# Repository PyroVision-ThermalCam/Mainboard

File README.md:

# PyroVision - Mainboard

## Table of Contents

- [PyroVision - Mainboard](#pyrovision---mainboard)
  - [Table of Contents](#table-of-contents)
  - [About](#about)
  - [License](#license)
  - [Maintainer](#maintainer)

## About

Mainboard for the PyroVision Open-Source Thermal Camera.

## License

This project is licensed under the GNU General Public License v3.0. See the [LICENSE](LICENSE) file for details.

## Maintainer

- [Daniel Kampert](mailto:daniel.kampert@kampis-elektroecke.de)

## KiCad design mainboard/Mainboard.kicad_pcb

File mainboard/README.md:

<h1 align="center">PyroVision Mainboard</h1>

<p align="center" width="100%">
  
</p>

***

<p align="center">
  
&nbsp; &nbsp; &nbsp; &nbsp;
  
</p>

***

## SPECIFICATIONS

| Parameter | Value |
| --- | --- |
| Dimensions | 32.0 × 24.0 mm |

***

## DIRECTORY STRUCTURE

    .
    ├─ Computations       # Misc calculations
    ├─ HTML               # HTML files for generated webpage
    ├─ Images             # Pictures and renders
    │
    ├─ kibot_resources    # External resources for KiBot
    │  ├─ colors          # Color theme for KiCad
    │  ├─ fonts           # Fonts used in the project
    │  ├─ scripts         # External scripts used with KiBot
    │  └─ templates       # Templates for KiBot generated reports
    │
    ├─ kibot_yaml         # KiBot YAML config files
    ├─ KiRI               # KiRI (PCB diff viewer) files
    │
    ├─ lib                # KiCad footprint and symbol libraries
    │  ├─ 3d_models       # Component 3D models
    │  ├─ lib_fp          # Footprint libraries
    │  └─ lib_sym         # Symbol libraries
    │
    ├─ logos              # Logos
    │
    ├─ Manufacturing      # Assembly and fabrication documents
    │  ├─ Assembly        # Assembly documents (BoM, pos, notes)
    │  │
    │  └─ Fabrication     # Fabrication documents (ZIP, notes)
    │     ├─ Drill Tables # CSV drill tables
    │     └─ Gerbers      # Gerbers
    │
    ├─ Report             # Reports for ERC/DRC
    ├─ Schematic          # PDF of schematic
    ├─ templates          # Title block templates
    ├─ Testing
    │  └─ Testpoints      # Testpoints tables
    │
    └─ Variants           # Outputs for assembly variants

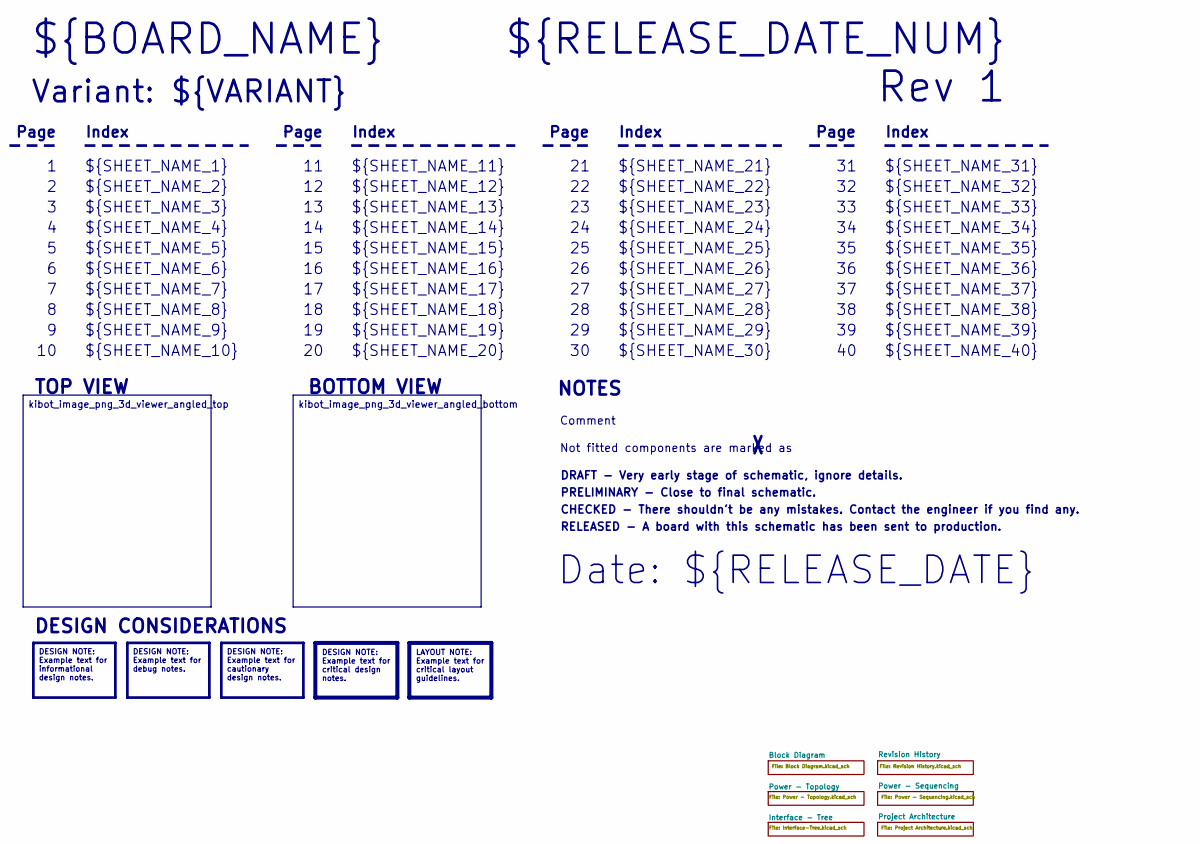
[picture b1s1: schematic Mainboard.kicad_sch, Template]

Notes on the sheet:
Variant: ${VARIANT}
RELEASED - A board with this schematic has been sent to production.
${SHEET_NAME_24}
Index
Page
PRELIMINARY - Close to final schematic.
${SHEET_NAME_22}
DRAFT - Very early stage of schematic, ignore details.
${SHEET_NAME_12}
${SHEET_NAME_8}
${SHEET_NAME_2}
${SHEET_NAME_5}
${SHEET_NAME_20}
${SHEET_NAME_23}
${RELEASE_DATE_NUM}
${SHEET_NAME_35}
Not fitted components are marked as
${SHEET_NAME_11}
${SHEET_NAME_6}
${SHEET_NAME_37}
${SHEET_NAME_26}
${SHEET_NAME_36}
Rev ${REVISION}
${SHEET_NAME_15}
CHECKED - There shouldn't be any mistakes. Contact the engineer if you find any.
BOTTOM VIEW
${SHEET_NAME_14}
${SHEET_NAME_21}
${SHEET_NAME_17}
${SHEET_NAME_18}
Date: ${RELEASE_DATE}
${SHEET_NAME_7}
${SHEET_NAME_31}
${BOARD_NAME}
NOTES
${SHEET_NAME_40}
${SHEET_NAME_39}
${SHEET_NAME_32}
${SHEET_NAME_1}
${SHEET_NAME_9}

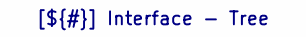
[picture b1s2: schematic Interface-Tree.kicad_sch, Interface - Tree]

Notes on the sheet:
[${#}] ${TITLE}

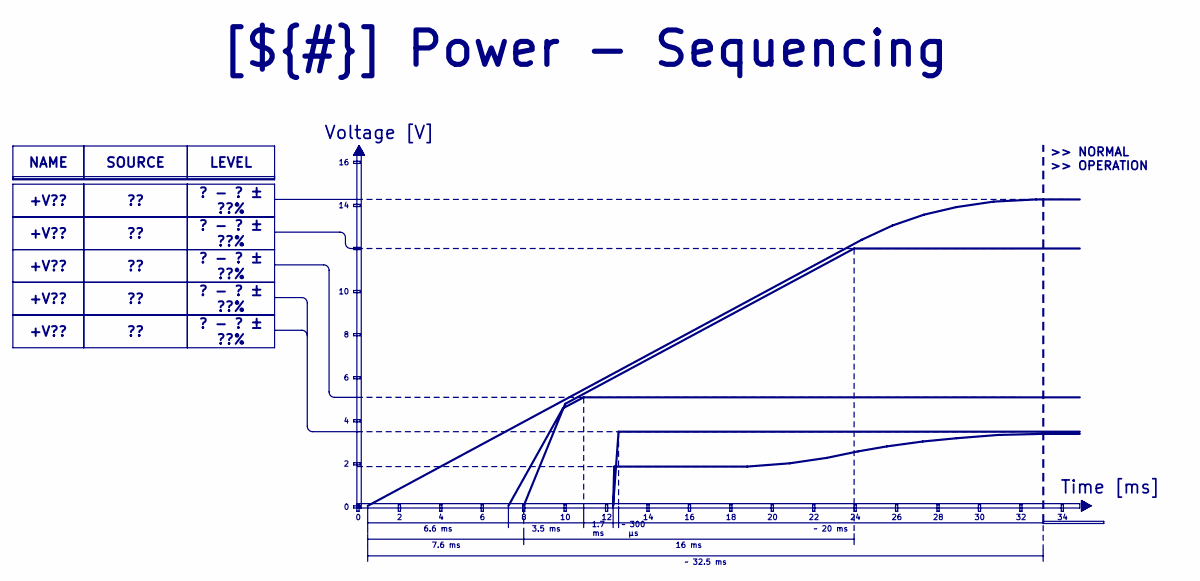
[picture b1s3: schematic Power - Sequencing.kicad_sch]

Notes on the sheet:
Voltage [V]
>> NORMAL >> OPERATION
Time [ms]
3.5 ms
7.6 ms
? - ? ± ??%
~ 300 μs
1.7 ms
16 ms
+V??
LEVEL
NAME
~ 20 ms
SOURCE
[${#}] ${TITLE}
6.6 ms
~ 32.5 ms

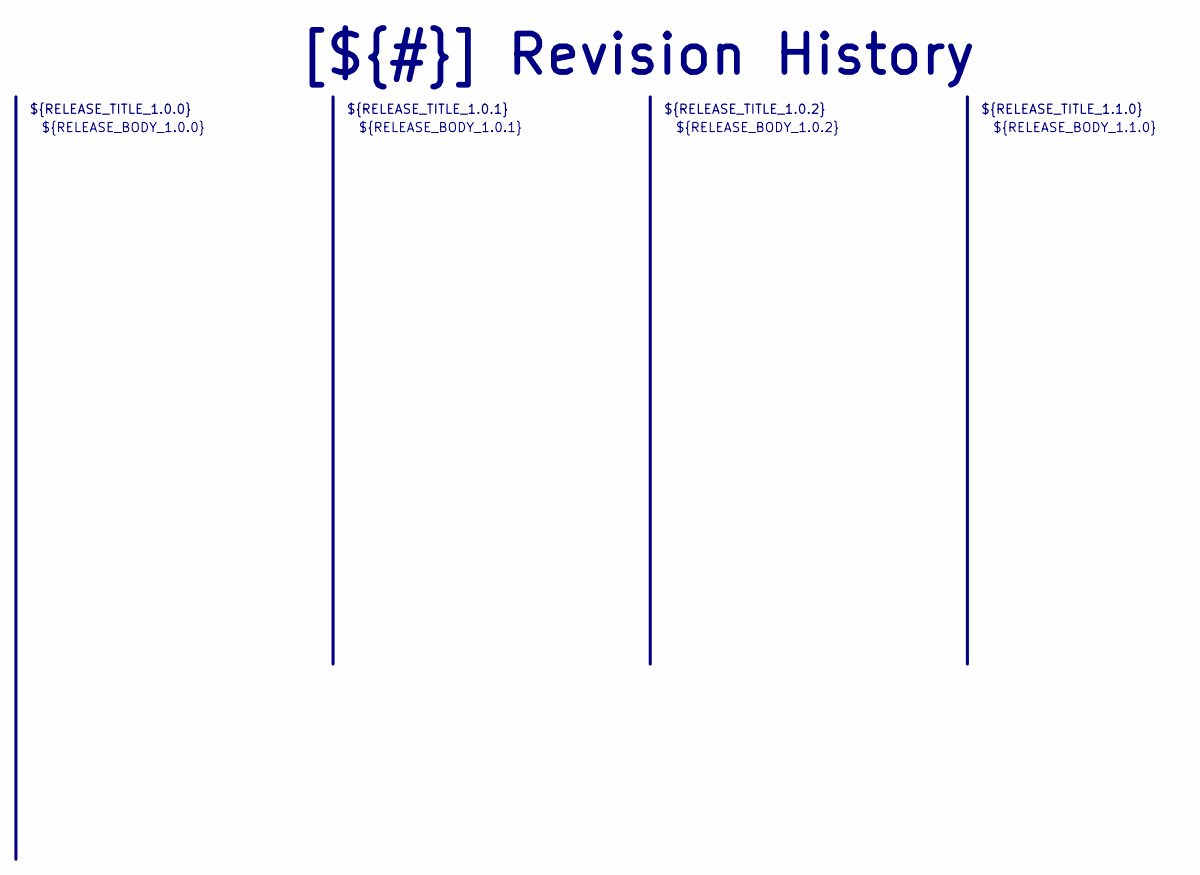
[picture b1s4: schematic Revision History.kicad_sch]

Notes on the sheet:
${RELEASE_BODY_1.1.0}
${RELEASE_BODY_1.0.0}
[${#}] ${TITLE}
${RELEASE_TITLE_1.0.2}
${RELEASE_BODY_1.0.2}
${RELEASE_BODY_1.0.1}
${RELEASE_TITLE_1.0.0}
${RELEASE_TITLE_1.0.1}
${RELEASE_TITLE_1.1.0}

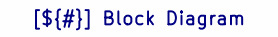
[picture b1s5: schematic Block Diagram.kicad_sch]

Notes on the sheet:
[${#}] ${TITLE}

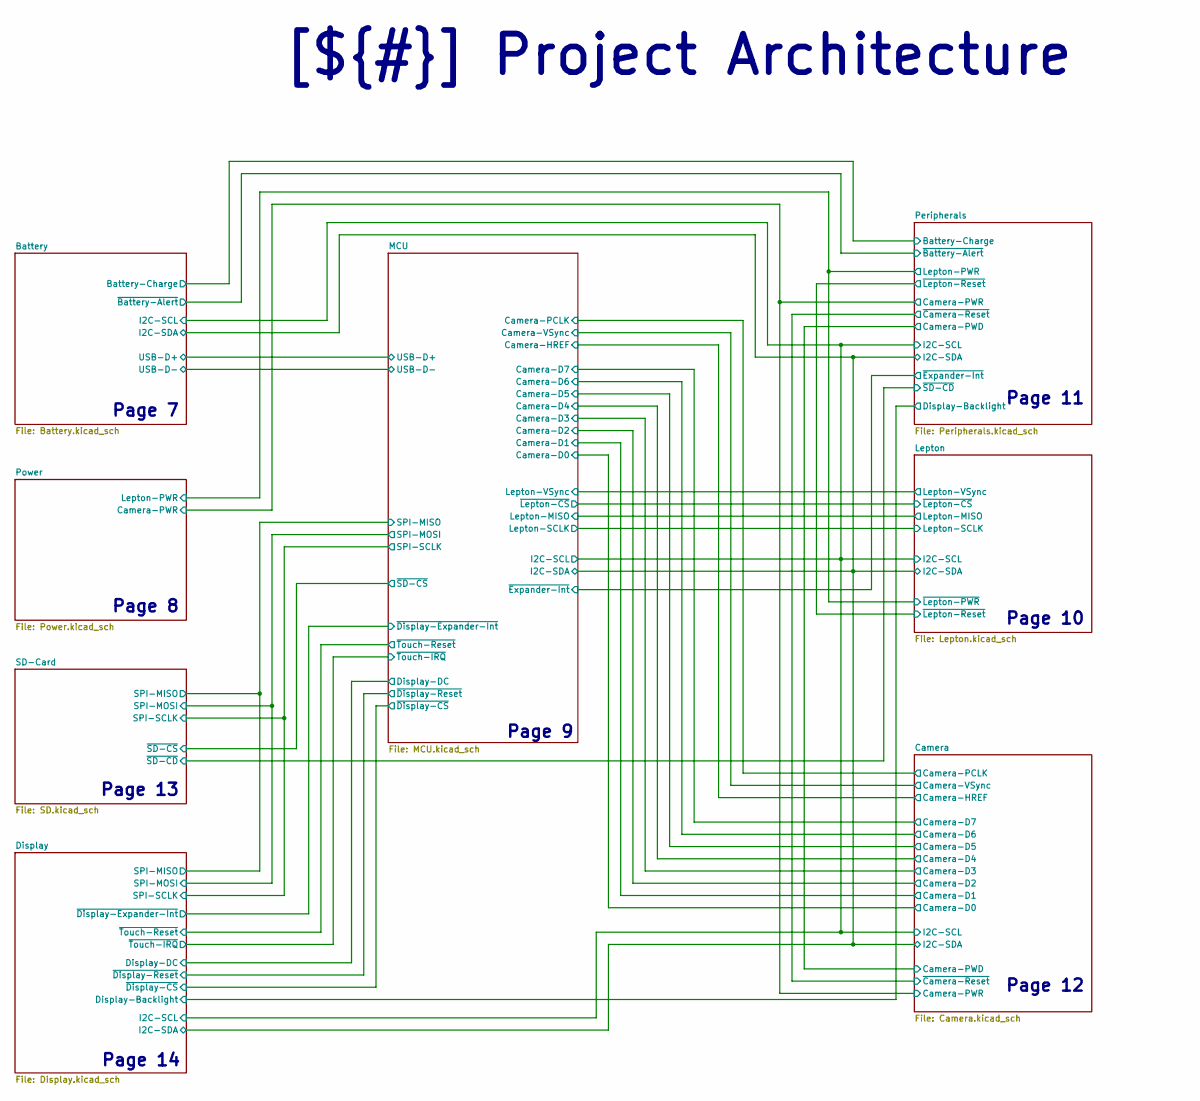
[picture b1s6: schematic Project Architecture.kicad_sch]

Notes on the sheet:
Page 12
Page 11
Page 13
Page 8
Page 10
Page 7
Page 14
Page 9
[${#}] ${TITLE}

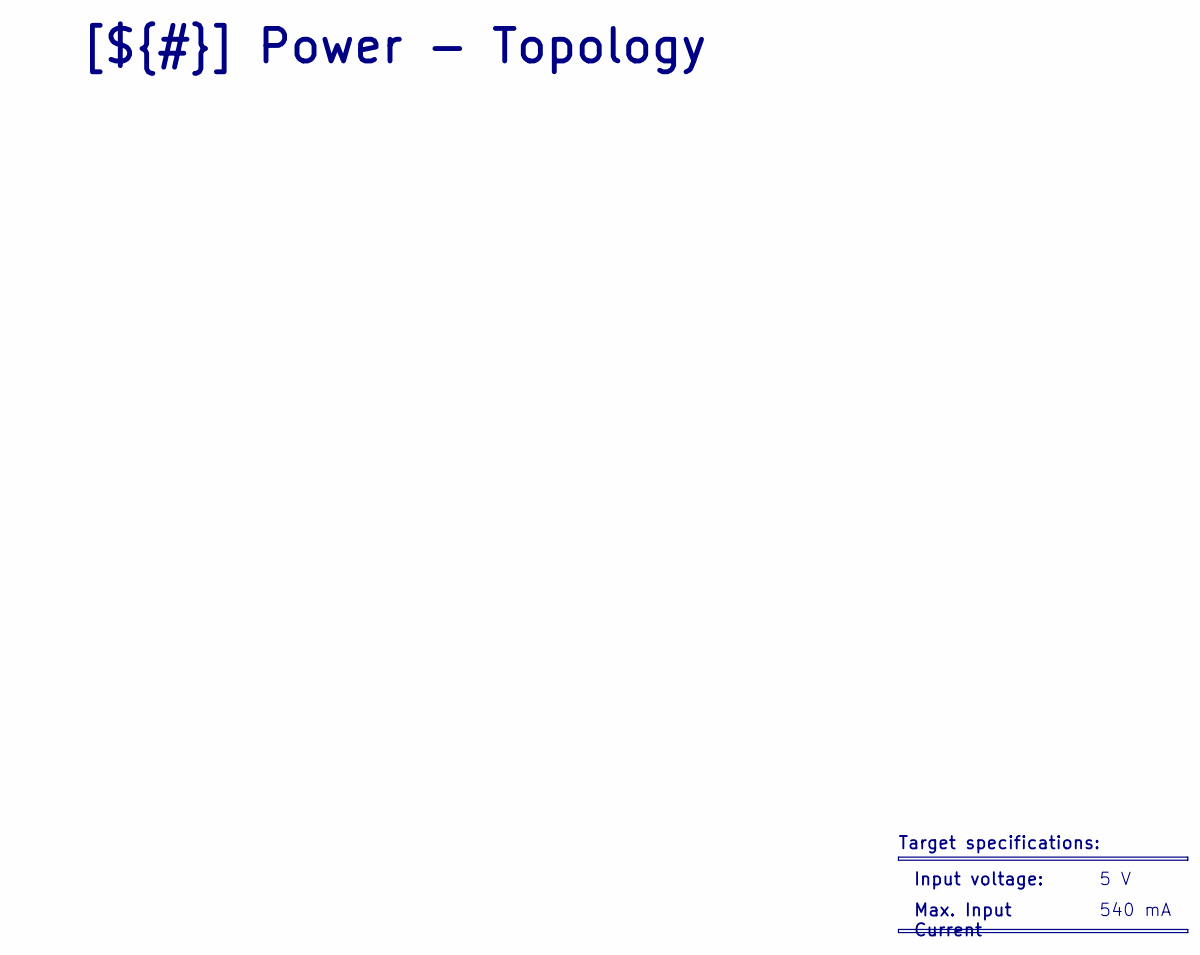
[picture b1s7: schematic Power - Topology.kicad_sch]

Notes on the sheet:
[${#}] ${TITLE}
Max. Input Current
Input voltage:
5 V
Target specifications:
540 mA

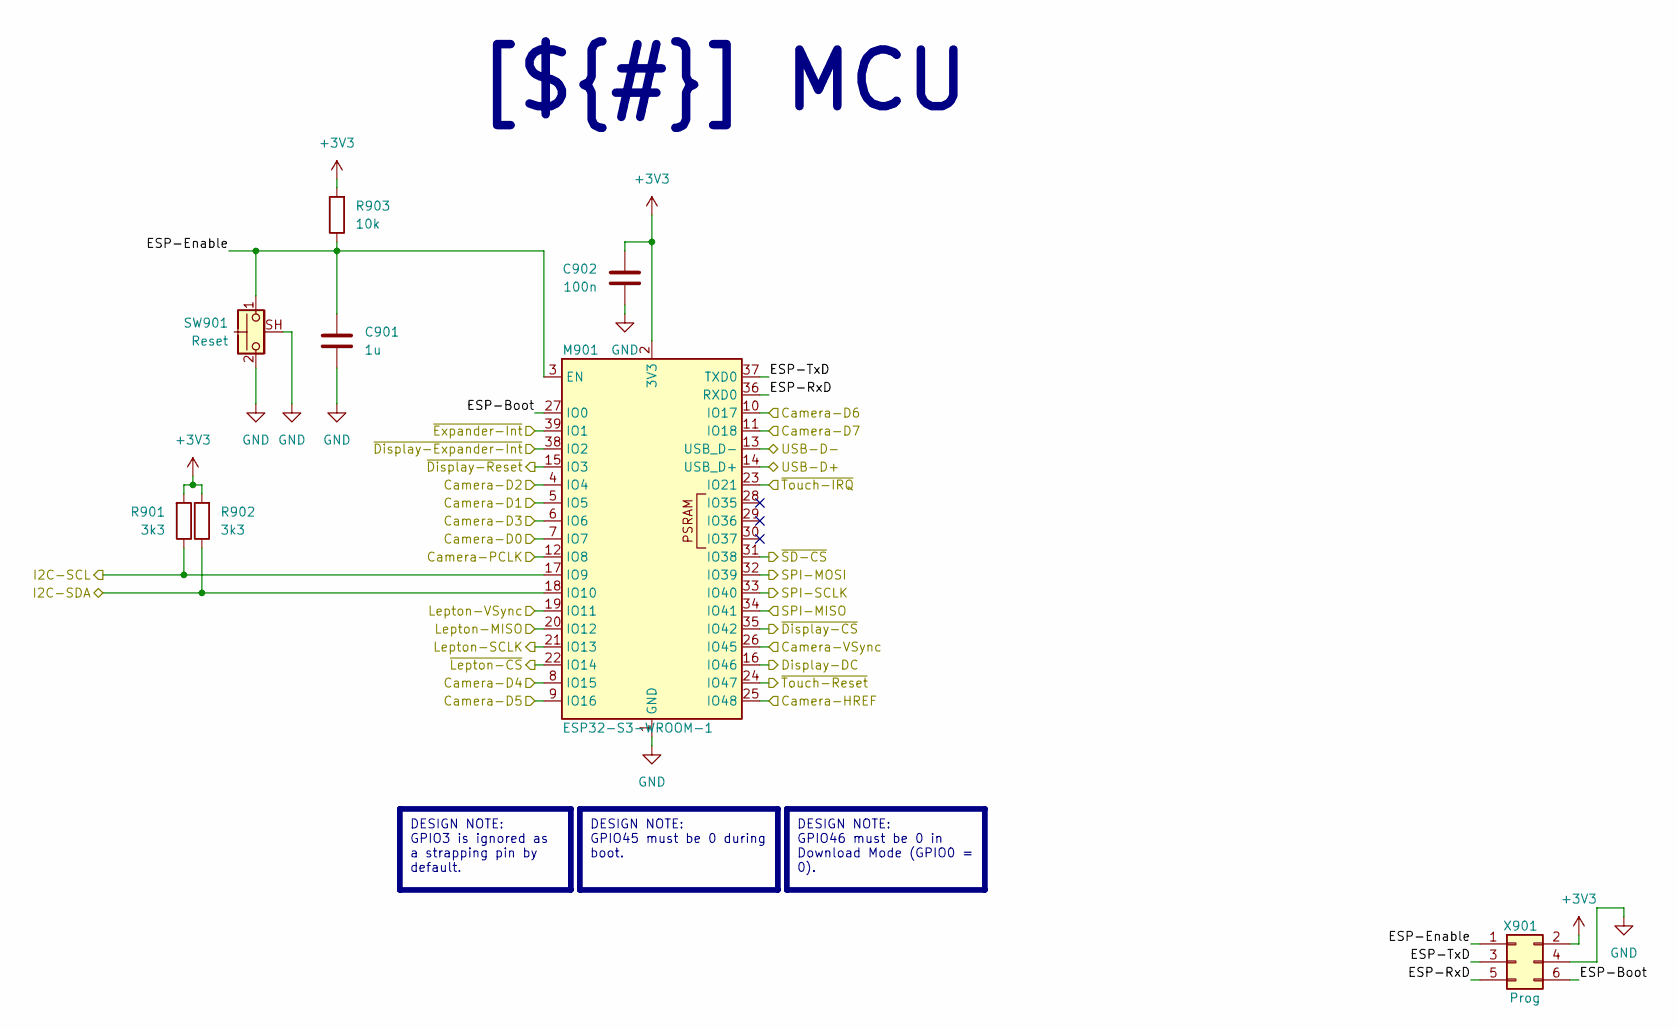
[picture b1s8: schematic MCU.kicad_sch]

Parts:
C901: 1u; C_0603_1608Metric; mouser# 581-06036C105MAT2A
C902: 100n; C_0603_1608Metric; mouser# 581-06031C104MAT2A
M901: ESP32-S3-WROOM-1; mouser# 356-ESP32-S3-WROOM-2-N32R16V
R901, R902: 3k3; R_0603_1608Metric; mouser# 603-RC0603FR-073K3L
R903: 10k; R_0603_1608Metric; mouser# 603-RC0603FR-073K3L
SW901: Reset; TS11; mouser# 179-TS1167443260RAD
X901: Prog; 490107670612-Debugging

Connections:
+3V3: C902.1, M901.2 (3V3), R901.2, R902.2, R903.2, X901.2; also elsewhere on the board
/Project Architecture/Battery/I2C-SCL: M901.17 (IO9), R901.1; also elsewhere on the board
/Project Architecture/Battery/I2C-SDA: M901.18 (IO10), R902.1; also elsewhere on the board
/Project Architecture/Battery/USB-D+: M901.14 (USB_D+); also elsewhere on the board
/Project Architecture/Battery/USB-D-: M901.13 (USB_D-); also elsewhere on the board
/Project Architecture/Camera/Camera-D0: M901.7 (IO7); also elsewhere on the board
/Project Architecture/Camera/Camera-D1: M901.5 (IO5); also elsewhere on the board
/Project Architecture/Camera/Camera-D2: M901.4 (IO4); also elsewhere on the board
/Project Architecture/Camera/Camera-D3: M901.6 (IO6); also elsewhere on the board
/Project Architecture/Camera/Camera-D4: M901.8 (IO15); also elsewhere on the board
/Project Architecture/Camera/Camera-D5: M901.9 (IO16); also elsewhere on the board
/Project Architecture/Camera/Camera-D6: M901.10 (IO17); also elsewhere on the board
/Project Architecture/Camera/Camera-D7: M901.11 (IO18); also elsewhere on the board
/Project Architecture/Camera/Camera-HREF: M901.25 (IO48); also elsewhere on the board
/Project Architecture/Camera/Camera-PCLK: M901.12 (IO8); also elsewhere on the board
/Project Architecture/Camera/Camera-VSync: M901.26 (IO45); also elsewhere on the board
/Project Architecture/Display/Display-DC: M901.16 (IO46); also elsewhere on the board
/Project Architecture/Display/SPI-MISO: M901.34 (IO41); also elsewhere on the board
/Project Architecture/Display/SPI-MOSI: M901.32 (IO39); also elsewhere on the board
/Project Architecture/Display/SPI-SCLK: M901.33 (IO40); also elsewhere on the board
/Project Architecture/Display/~Display-CS: M901.35 (IO42); also elsewhere on the board
/Project Architecture/Display/~Display-Expander-Int: M901.38 (IO2); also elsewhere on the board
/Project Architecture/Display/~Display-Reset: M901.15 (IO3); also elsewhere on the board
/Project Architecture/Display/~Touch-IRQ: M901.23 (IO21); also elsewhere on the board
/Project Architecture/Display/~Touch-Reset: M901.24 (IO47); also elsewhere on the board
/Project Architecture/Lepton/Lepton-MISO: M901.20 (IO12); also elsewhere on the board
/Project Architecture/Lepton/Lepton-SCLK: M901.21 (IO13); also elsewhere on the board
/Project Architecture/Lepton/Lepton-VSync: M901.19 (IO11); also elsewhere on the board
/Project Architecture/Lepton/~Lepton-CS: M901.22 (IO14); also elsewhere on the board
/Project Architecture/MCU/ESP-Boot: M901.27 (IO0), X901.6
/Project Architecture/MCU/ESP-Enable: C901.1, M901.3 (EN), R903.1, SW901.1, X901.1
/Project Architecture/MCU/ESP-RxD: M901.36 (RXD0), X901.5
/Project Architecture/MCU/ESP-TxD: M901.37 (TXD0), X901.3
/Project Architecture/MCU/~Expander-Int: M901.39 (IO1); also elsewhere on the board
/Project Architecture/MCU/~SD-CS: M901.31 (IO38); also elsewhere on the board
GND: C901.2, C902.2, M901.1 (GND), M901.40 (GND), M901.41 (GND), SW901.2, SW901.SH (B), X901.4; also elsewhere on the board

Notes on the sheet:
DESIGN NOTE: GPIO45 must be 0 during boot.
DESIGN NOTE: GPIO46 must be 0 in Download Mode (GPIO0 = 0).
DESIGN NOTE: GPIO3 is ignored as a strapping pin by default.
[${#}] ${TITLE}

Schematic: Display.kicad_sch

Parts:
R1401, R1402, R1403, R1404, R1405: 100k; R_0603_1608Metric; mouser# 652-CR0603-JW-104ELF
X1401: Displayboard; Amphenol_F32R-1A7x1-11014_1x14-1MP_P0.5mm_Horizontal; mouser# 649-F32R-1A7H1-11014

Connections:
+3V3: R1401.2, R1402.2, R1403.2, R1404.2, R1405.2, X1401.14; also elsewhere on the board
/Project Architecture/Battery/I2C-SCL: X1401.9; also elsewhere on the board
/Project Architecture/Battery/I2C-SDA: X1401.10; also elsewhere on the board
/Project Architecture/Display/Display-Backlight: X1401.1; also elsewhere on the board
/Project Architecture/Display/Display-DC: X1401.5; also elsewhere on the board
/Project Architecture/Display/SPI-MISO: X1401.2; also elsewhere on the board
/Project Architecture/Display/SPI-MOSI: X1401.3; also elsewhere on the board
/Project Architecture/Display/SPI-SCLK: X1401.6; also elsewhere on the board
/Project Architecture/Display/~Display-CS: R1401.1, X1401.4; also elsewhere on the board
/Project Architecture/Display/~Display-Expander-Int: R1404.1, X1401.8; also elsewhere on the board
/Project Architecture/Display/~Display-Reset: R1405.1, X1401.7; also elsewhere on the board
/Project Architecture/Display/~Touch-IRQ: R1403.1, X1401.11; also elsewhere on the board
/Project Architecture/Display/~Touch-Reset: R1402.1, X1401.12; also elsewhere on the board
GND: X1401.13, X1401.MP (MountPin); also elsewhere on the board

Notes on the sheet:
6. SPI-SCLK
10. SDA
12. ~{Touch-Reset}
7. ~{Display-Reset}
13. GND
1. Display-Backlight
4. ~{Display-CS}
5. Display-DC
11. ~{Touch-IRQ}
3. SPI-MOSI
8. ~{Display-Expander-Int}
14. +3V3
2. SPI-MISO
9. SCL
[${#}] ${TITLE}

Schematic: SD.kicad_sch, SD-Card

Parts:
C1301: 100n; C_0603_1608Metric; mouser# 581-06031C104MAT2A
R1301: 100k; R_0603_1608Metric; mouser# 652-CR0603-JW-104ELF; not fitted
X1301: Micro SD-Card; MSD-4-A; mouser# 179-MSD-4-A

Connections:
+3V3: R1301.2, X1301.4 (VDD); also elsewhere on the board
/Project Architecture/Display/SPI-MISO: X1301.7 (DAT0); also elsewhere on the board
/Project Architecture/Display/SPI-MOSI: X1301.3 (CMD); also elsewhere on the board
/Project Architecture/Display/SPI-SCLK: X1301.5 (CLK); also elsewhere on the board
/Project Architecture/MCU/~SD-CS: X1301.2 (DAT3/CD); also elsewhere on the board
/Project Architecture/Peripherals/~SD-CD: C1301.1, R1301.1, X1301.9 (DET); also elsewhere on the board
GND: C1301.2, X1301.6 (VSS), X1301.10 (SHIELD); also elsewhere on the board

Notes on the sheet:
[${#}] ${TITLE}

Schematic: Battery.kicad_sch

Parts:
C701, C702: 1u; C_0603_1608Metric; mouser# 581-06036C105MAT2A
C703: 100n; C_0603_1608Metric; mouser# 581-06031C104MAT2A
F701: 6 V / 4.5 A; Fuse_1206_3216Metric; mouser# 576-1206L450SLWR
IC701: USBLC6-2P6; SOT-666; mouser# 511-USBLC6-2P6
IC702: BQ21040DBV; SOT-23-6; mouser# 595-BQ21040DBVR
IC703: MAX17048; TDFN-8-1EP_2x2mm_P0.5mm_EP0.8x1.2mm; mouser# 700-MAX17048G+T10
Q701: Si2333CDS; SOT-23-3; mouser# 78-SI2333CDS-T1-BE3
R701, R702: 5k1; R_0603_1608Metric; mouser# 652-CR0603-JW-512ELF
R703, R709: 1k; R_0603_1608Metric; mouser# 652-CR0603-JW-102ELF
R704, R710: 100k; R_0603_1608Metric; mouser# 652-CR0603-JW-104ELF; not fitted
R705, R708: 0R; R_1206_3216Metric; mouser# 652-CR1206-J/-000ELF; not fitted
R706, R707, R711: 0R; R_1206_3216Metric; mouser# 652-CR1206-J/-000ELF
TH701: 10k; R_0603_1608Metric; mouser# 603-RC0603FR-073K3L
TP701, TP702, TP703: TestPoint_Pad_1.0x1.0mm
X701: USB; USB_C_Receptacle_GCT_USB4110; mouser# 640-USB4110-GF-A
X702: Battery; S2B-PH-SM4-TB; mouser# 306-S2B-PH-SM4-TB(LF)(SN)

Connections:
+3V3: R704.2, R710.2; also elsewhere on the board
+BATT: R711.2, TP703.1; also elsewhere on the board
/Project Architecture/Battery/Battery-Charge: IC702.3 (~CHG), R704.1; also elsewhere on the board
/Project Architecture/Battery/I2C-SCL: IC703.7 (SCL); also elsewhere on the board
/Project Architecture/Battery/I2C-SDA: IC703.8 (SDA); also elsewhere on the board
/Project Architecture/Battery/USB-D+: IC701.4 (I/O2); also elsewhere on the board
/Project Architecture/Battery/USB-D-: IC701.6 (I/O1); also elsewhere on the board
/Project Architecture/Battery/VBat: C702.1, F701.1, IC702.2 (OUT), R705.2, R707.2, TP701.1
/Project Architecture/Battery/~Battery-Alert: IC703.5 (~ALERT), R710.1, TP702.1; also elsewhere on the board
GND: C701.2, C702.2, C703.2, IC701.2 (GND), IC702.5 (GND), IC703.1 (CTG), IC703.4 (GND), IC703.6 (QSTRT), IC703.9 (EP), R701.1, R702.1, R703.1, R706.1, R708.2, R709.1, TH701.2, X701.A1 (GND), X701.A12 (GND), X701.B1 (GND), X701.B12 (GND), X701.S1 (SHIELD); also elsewhere on the board
unnamed: IC701.1 (I/O1), X701.A7 (D-), X701.B7 (D-)
unnamed: IC701.3 (I/O2), X701.A6 (D+), X701.B6 (D+)
unnamed: C701.1, IC701.5 (VBUS), IC702.6 (VIN), X701.A4 (VBUS), X701.A9 (VBUS), X701.B4 (VBUS), X701.B9 (VBUS)
unnamed: IC702.4 (ISET), R703.2
unnamed: IC702.1 (TS), TH701.1
unnamed: C703.1, IC703.2 (CELL), IC703.3 (VDD), Q701.2 (S), R711.1
unnamed: F701.2, Q701.3 (D)
unnamed: Q701.1 (G), R709.2
unnamed: R702.2, X701.A5 (CC1)
unnamed: R701.2, X701.B5 (CC2)
unnamed: R705.1, R706.2, X702.1
unnamed: R707.1, R708.1, X702.2

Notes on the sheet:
[${#}] ${TITLE}
LAYOUT NOTE: 90 Ohms ± 15%
DESIGN NOTE: Can be replaced with static 10k, if not needed.
DESIGN NOTE: Calculated for a charging current of 540 mA.
Battery connector
DESIGN NOTE: These resistors can be used to swap the polarity of the battery connector.
Reverse and overcurrent protection
LiPo Charger
LiPo Gauge

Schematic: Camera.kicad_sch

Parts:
C1201: 10n; C_0603_1608Metric; mouser# 581-06035A103KAT2A
IC1201: TXB0102DCU; VSSOP-8_2.3x2mm_P0.5mm; mouser# 595-TXB0102DCUR
IC1202: PCA9306JK; XSON-8_0.65x0.17mm_P0.35mm; mouser# 771-PCA9306JKZ
R1201: 0R; R_0603_1608Metric; mouser# 652-CR1206-J/-000ELF
R1202, R1203: 100k; R_0603_1608Metric; mouser# 652-CR0603-JW-104ELF
R1204, R1205: 2k8; R_0603_1608Metric; mouser# 603-RC0603FR-072K8L
R1206: 200k; R_0603_1608Metric; mouser# 603-RC0603FR-07200KL
X1201: Camera; Amphenol_F32R-1A7x1-11024_1x24-1MP_P0.5mm_Horizontal; mouser# 649-F32R-1A7H1-11024
Y1201: 25 MHz; Oscillator_SMD_Abracon_ASDMB-4Pin_2.5x2.0mm; mouser# 815-ASDDV2500MHZLCT3

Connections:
+3V3: IC1201.3 (VCCA), IC1201.6 (OE), R1201.2, R1203.2, R1206.1; also elsewhere on the board
/Project Architecture/Battery/I2C-SCL: IC1202.6 (SCL_{2}); also elsewhere on the board
/Project Architecture/Battery/I2C-SDA: IC1202.5 (SDA_{2}); also elsewhere on the board
/Project Architecture/Camera/Camera-D0: X1201.6; also elsewhere on the board
/Project Architecture/Camera/Camera-D1: X1201.4; also elsewhere on the board
/Project Architecture/Camera/Camera-D2: X1201.3; also elsewhere on the board
/Project Architecture/Camera/Camera-D3: X1201.5; also elsewhere on the board
/Project Architecture/Camera/Camera-D4: X1201.7; also elsewhere on the board
/Project Architecture/Camera/Camera-D5: X1201.9; also elsewhere on the board
/Project Architecture/Camera/Camera-D6: X1201.11; also elsewhere on the board
/Project Architecture/Camera/Camera-D7: X1201.13; also elsewhere on the board
/Project Architecture/Camera/Camera-HREF: X1201.16; also elsewhere on the board
/Project Architecture/Camera/Camera-PCLK: X1201.8; also elsewhere on the board
/Project Architecture/Camera/Camera-PWD: IC1201.4 (A2), R1203.1; also elsewhere on the board
/Project Architecture/Camera/Camera-PWD_{LV}: IC1201.1 (B2), X1201.17
/Project Architecture/Camera/Camera-VSync: X1201.18; also elsewhere on the board
/Project Architecture/Camera/MCLK: X1201.12, Y1201.3 (OUT)
/Project Architecture/Camera/SCL_{LV}: IC1202.3 (SCL_{1}), R1204.1, X1201.20
/Project Architecture/Camera/SDA_{LV}: IC1202.4 (SDA_{1}), R1205.1, X1201.22
/Project Architecture/Camera/~Camera-Reset: IC1201.5 (A1), R1202.2; also elsewhere on the board
/Project Architecture/Camera/~Camera-Reset_{LV}: IC1201.8 (B1), X1201.19
Camera-1V5: X1201.15; also elsewhere on the board
Camera-2V8: C1201.1, IC1201.7 (VCCB), IC1202.2 (VCC_{1}), R1204.2, R1205.2, X1201.14, X1201.21, Y1201.1 (Tri-State), Y1201.4 (VDD); also elsewhere on the board
GND: C1201.2, IC1201.2 (GND), IC1202.1 (GND), R1202.1, X1201.1, X1201.10, X1201.23, X1201.MP (MountPin), Y1201.2 (GND); also elsewhere on the board
unnamed: IC1202.7 (VCC_{2}), IC1202.8 (EN), R1206.2
unnamed: R1201.1, X1201.2

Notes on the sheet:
14. DOVDD
16. HREF
17. PWDN
21. AVDD
15. DVDD
5. Y5
9. Y7
10. DGND
2. Y1
11. Y8
4. Y3
1. Y0
22 SIO_D
19. RST
12. XCLK
6. Y2
24. NC
20. SIO_C
3. Y4
8. PCLK
18. VSYNC
7. Y6
13. Y9
23. AGND
DESIGN NOTE: The camera use an internal pull-down.
OV5640 camera connector
DESIGN NOTE: The camera use an internal pull-up.
[${#}] ${TITLE}
Level shifting (Camera IO <> System Voltage)
DESIGN NOTE: This pin is used for the AF power supply.

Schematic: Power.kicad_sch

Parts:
C801: 4u7; C_0603_1608Metric; mouser# 581-06036D475MAT4A
C802, C803, C804, C805, C807, C808, C809, C810, C811, C812: 1u; C_0603_1608Metric; mouser# 581-06036C105MAT2A
C806: 10u; C_0603_1608Metric; mouser# 581-06034D106K
IC801, IC805: LP5907MFX-2.8; SOT-23-5; mouser# 595-LP5907MFX-2.8/NOPB
IC802: LP5907MFX-1.5; SOT-23-5; mouser# 595-LP5907MFX-1.5/NOPB
IC803: TPS62823DLC; Texas_VSON-HR-8_1.5x2mm_P0.5mm; mouser# 595-TPS62823DLCR
IC804: LP5907MFX-3.0; SOT-23-5; mouser# 595-LP5907MFX-3.0NPB
IC806: LP5907MFX-1.2; SOT-23-5; mouser# 595-LP5907MFX-1.2/NOPB
L801: 470n; L_Murata_DFE201610P; mouser# 81-DFE201610E-R47MP2
R801: 100k; R_0603_1608Metric; mouser# 652-CR0603-JW-104ELF
R802, R803, R806, R807, R808: 100k; R_0603_1608Metric; mouser# 652-CR0603-JW-104ELF; not fitted
R804: 45k3; R_0603_1608Metric; mouser# 652-CR0603-FX-4532ELF
R805: 10k; R_0603_1608Metric; mouser# 603-RC0603FR-0710KL
SW801: On / Off; SW_Slide_SPDT_Angled_CK_OS102011MA1Q; mouser# 611-OS102011MA1QN1
TP801, TP802, TP803, TP804, TP805, TP806: TestPoint_Pad_1.0x1.0mm

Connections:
+3V3: C802.1, C803.1, C806.1, C807.1, C808.1, C809.1, IC801.1 (IN), IC802.1 (IN), IC804.1 (IN), IC805.1 (IN), IC806.1 (IN), L801.2, R804.1, TP803.1; also elsewhere on the board
+BATT: C801.1, IC803.7 (VIN), SW801.3 (C); also elsewhere on the board
/Project Architecture/Lepton/~Lepton-PWR: IC804.3 (EN), IC805.3 (EN), IC806.3 (EN), R806.1, R807.1, R808.1; also elsewhere on the board
/Project Architecture/Peripherals/Camera-PWR: IC801.3 (EN), IC802.3 (EN), R802.1, R803.1; also elsewhere on the board
Camera-1V5: C805.1, IC802.5 (OUT), TP802.1; also elsewhere on the board
Camera-2V8: C804.1, IC801.5 (OUT), TP801.1; also elsewhere on the board
GND: C801.2, C802.2, C803.2, C804.2, C805.2, C806.2, C807.2, C808.2, C809.2, C810.2, C811.2, C812.2, IC801.2 (GND), IC802.2 (GND), IC803.3 (AGND), IC803.5 (PGND), IC804.2 (GND), IC805.2 (GND), IC806.2 (GND), R801.2, R802.2, R803.2, R805.2, R806.2, R807.2, R808.2; also elsewhere on the board
Lepton-1V2: C812.1, IC806.5 (OUT), TP806.1; also elsewhere on the board
Lepton-2V8: C811.1, IC805.5 (OUT), TP805.1; also elsewhere on the board
Lepton-3V0: C810.1, IC804.5 (OUT), TP804.1; also elsewhere on the board
unnamed: IC803.1 (EN), SW801.2 (B)
unnamed: IC803.2 (FB), R804.2, R805.1
unnamed: IC803.6 (SW), L801.1
unnamed: R801.1, SW801.1 (A)

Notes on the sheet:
VDDC (0.3 W)
VDDA (0.7 W)
VDDIO (1.5 W)
+3V3 (9.9 W)
VDD (0.7 W)
VDDC (0.375 W)
Main Power
Lepton Power
DESIGN NOTE: I_{DDIO} is specified with up to 310 mA.
Camera Power
[${#}] ${TITLE}

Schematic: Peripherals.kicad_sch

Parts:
C1101, C1102, C1103, C1104, C1105, C1106: 100n; C_0603_1608Metric; mouser# 581-06031C104MAT2A
C1107: 4u7; C_0603_1608Metric; mouser# 581-06036D475MAT4A
D1101, D1102: Flash; XP-G; mouser# 941-XPGDWT-BS-0000-00P5E
IC1101: PCAL6416AHF; HVQFN-24-1EP_4x4mm_P0.5mm_EP2.1x2.1mm; mouser# 771-PCAL6416AHF,128
IC1102: TMP117xxYBG; WSON-6-1EP_2x2mm_P0.65mm_EP1x1.6mm; mouser# 595-TMP117MAIDRVR
IC1103: PCA9306JK; XSON-8_0.65x0.17mm_P0.35mm; mouser# 771-PCA9306JKZ
IC1104: PCA9633DP1,118; TSSOP-8_3x3mm_P0.65mm; mouser# 771-PCA9633DP1,118
IC1105: RV-8263-C8; mouser# 428-204291-MC01
IC1106: VL53L1CXV0FY1; ST_VL53L1x; mouser# 511-VL53L1CXV0FY/1
Q1101, Q1102: DMN2053UQ; SOT-23; mouser# 621-DMN2053UQ-7
R1101, R1102, R1103, R1106, R1115: 100k; R_0603_1608Metric; mouser# 652-CR0603-JW-104ELF
R1104, R1107: 10R; R_1206_3216Metric; mouser# 71-RCA120610R0FKEASR
R1105, R1108, R1109, R1113, R1114: 3k3; R_0603_1608Metric; mouser# 603-RC0603FR-073K3L; not fitted
R1110: 200k; R_0603_1608Metric; mouser# 603-RC0603FR-07200KL
R1111, R1112: 3k3; R_0603_1608Metric; mouser# 603-RC0603FR-073K3L
TP1101, TP1102, TP1103, TP1104, TP1105, TP1106, TP1107, TP1108, TP1109, TP1110, TP1111, TP1112, TP1113: TestPoint_Pad_1.0x1.0mm

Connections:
+3V3: C1102.1, C1103.1, C1104.1, C1106.1, C1107.1, IC1101.21 (V_{DD(P)}), IC1101.23 (V_{DD(I2C-bus)}), IC1102.5 (V+), IC1103.2 (VCC_{1}), IC1104.8 (VDD), IC1106.1 (AVDDVCSEL), IC1106.11 (AVDD), R1101.2, R1102.2, R1105.2, R1108.2, R1109.2, R1113.2, R1114.2, R1115.1; also elsewhere on the board
+BATT: C1105.1, IC1105.5 (V_{DD}), R1104.2, R1107.2, R1110.1, R1111.2, R1112.2; also elsewhere on the board
/Project Architecture/Battery/Battery-Charge: IC1101.2 (P0_1), TP1109.1; also elsewhere on the board
/Project Architecture/Battery/I2C-SCL: IC1101.19 (SCL), IC1102.1 (SCL), IC1103.3 (SCL_{1}), IC1104.6 (SCL), IC1106.10 (SCL), R1108.1, TP1102.1; also elsewhere on the board
/Project Architecture/Battery/I2C-SDA: IC1101.20 (SDA), IC1102.6 (SDA), IC1103.4 (SDA_{1}), IC1104.7 (SDA), IC1106.9 (SDA), R1109.1, TP1101.1; also elsewhere on the board
/Project Architecture/Battery/~Battery-Alert: IC1101.1 (P0_0); also elsewhere on the board
/Project Architecture/Camera/Camera-PWD: IC1101.13 (P1_3); also elsewhere on the board
/Project Architecture/Camera/~Camera-Reset: IC1101.16 (P1_6), TP1104.1; also elsewhere on the board
/Project Architecture/Display/Display-Backlight: IC1104.3 (LED2); also elsewhere on the board
/Project Architecture/Lepton/~Lepton-PWR: IC1101.4 (P0_3), TP1105.1; also elsewhere on the board
/Project Architecture/Lepton/~Lepton-Reset: IC1101.15 (P1_5), TP1106.1; also elsewhere on the board
/Project Architecture/MCU/~Expander-Int: IC1101.22 (~INT), R1102.1; also elsewhere on the board
/Project Architecture/Peripherals/Camera-PWR: IC1101.17 (P1_7), TP1103.1; also elsewhere on the board
/Project Architecture/Peripherals/LED-Flash_{1}: IC1104.2 (LED1), Q1101.1 (G), R1103.2, TP1112.1
/Project Architecture/Peripherals/LED-Flash_{2}: IC1104.1 (LED0), Q1102.1 (G), R1106.2, TP1113.1
/Project Architecture/Peripherals/~RTC-INT: IC1101.5 (P0_4), IC1105.3 (~INT), R1114.1, TP1108.1
/Project Architecture/Peripherals/~Range-INT: IC1101.8 (P0_7), IC1106.7 (GPIO1), R1113.1, TP1110.1
/Project Architecture/Peripherals/~SD-CD: IC1101.14 (P1_4), TP1107.1; also elsewhere on the board
/Project Architecture/Peripherals/~Temp-INT: IC1101.7 (P0_6), IC1102.3 (ALERT), R1105.1, TP1111.1
GND: C1101.2, C1102.2, C1103.2, C1104.2, C1105.2, C1106.2, C1107.2, IC1101.9 (V_{SS}), IC1101.18 (ADDR), IC1101.25 (EP), IC1102.2 (GND), IC1102.4 (ADD0), IC1103.1 (GND), IC1104.5 (GND), IC1105.2 (CLKOE), IC1105.4 (GND), IC1106.2 (AVSSVCSEL), IC1106.3 (GND), IC1106.4 (GND), IC1106.6 (GND), IC1106.12 (GND), Q1101.2 (S), Q1102.2 (S), R1103.1, R1106.1; also elsewhere on the board
unnamed: D1101.2 (A), R1104.1
unnamed: D1101.1 (K), Q1101.3 (D)
unnamed: D1102.2 (A), R1107.1
unnamed: D1102.1 (K), Q1102.3 (D)
unnamed: C1101.1, IC1101.24 (~RESET), R1101.1
unnamed: IC1103.7 (VCC_{2}), IC1103.8 (EN), R1110.2
unnamed: IC1103.6 (SCL_{2}), IC1105.8 (SCL), R1111.1
unnamed: IC1103.5 (SDA_{2}), IC1105.1 (SDA), R1112.1
unnamed: IC1106.5 (XSHUT), R1115.2

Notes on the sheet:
ToF Sensor
LED-Flash
PWM-Controller
Test points
Port Expander
Temperatur sensor
[${#}] ${TITLE}
RTC and Level shifting (RTC IO <> System Voltage)

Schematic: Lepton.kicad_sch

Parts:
C1001, C1002, C1004: 100n; C_0603_1608Metric; mouser# 581-06031C104MAT2A
C1003: 10n; C_0603_1608Metric; mouser# 581-06035A103KAT2A
IC1001, IC1003: TXB0104RUT; Texas_R-PUQFN-N12; mouser# 595-TXB0104RUTR
IC1002: PCA9306JK; XSON-8_0.65x0.17mm_P0.35mm; mouser# 771-PCA9306JKZ
R1001, R1003: 100k; R_0603_1608Metric; mouser# 652-CR0603-JW-104ELF
R1002: 0R; R_0603_1608Metric; mouser# 652-CR1206-J/-000ELF
R1004, R1005: 3k3; R_0603_1608Metric; mouser# 603-RC0603FR-073K3L
R1006: 200k; R_0603_1608Metric; mouser# 603-RC0603FR-07200KL
TP1001: TestPoint_Pad_1.0x1.0mm
X1001: LEPTON; 105028-1001; mouser# 538-105028-1001
Y1001: 25 MHz; Oscillator_SMD_Abracon_ASDMB-4Pin_2.5x2.0mm; mouser# 815-ASDDV2500MHZLCT3

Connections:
+3V3: IC1001.1 (VCCA), IC1001.12 (OE), IC1003.1 (VCCA), IC1003.12 (OE), R1006.1; also elsewhere on the board
/Project Architecture/Battery/I2C-SCL: IC1002.6 (SCL_{2}); also elsewhere on the board
/Project Architecture/Battery/I2C-SDA: IC1002.5 (SDA_{2}); also elsewhere on the board
/Project Architecture/Lepton/Lepton-MISO: IC1003.4 (A3); also elsewhere on the board
/Project Architecture/Lepton/Lepton-MISO_{LV}: IC1003.8 (B3), X1001.12
/Project Architecture/Lepton/Lepton-SCLK: IC1003.3 (A2); also elsewhere on the board
/Project Architecture/Lepton/Lepton-SCLK_{LV}: IC1003.9 (B2), X1001.13
/Project Architecture/Lepton/Lepton-VSync: IC1001.5 (A4); also elsewhere on the board
/Project Architecture/Lepton/Lepton-VSync_{LV}: IC1001.7 (B4), X1001.2
/Project Architecture/Lepton/SCL_{LV}: IC1002.3 (SCL_{1}), R1004.1, X1001.21
/Project Architecture/Lepton/SDA_{LV}: IC1002.4 (SDA_{1}), R1005.1, X1001.22
/Project Architecture/Lepton/~Lepton-CS: IC1003.2 (A1); also elsewhere on the board
/Project Architecture/Lepton/~Lepton-CS_{LV}: IC1003.10 (B1), X1001.14
/Project Architecture/Lepton/~Lepton-PWR: IC1001.3 (A2); also elsewhere on the board
/Project Architecture/Lepton/~Lepton-PWR_{LV}: IC1001.9 (B2), R1001.2, X1001.23
/Project Architecture/Lepton/~Lepton-Reset: IC1001.4 (A3); also elsewhere on the board
/Project Architecture/Lepton/~Lepton-Reset_{LV}: IC1001.8 (B3), R1003.2, X1001.24
GND: C1001.2, C1002.2, C1003.2, C1004.2, IC1001.6 (GND), IC1002.1 (GND), IC1003.6 (GND), R1002.2, X1001.1, X1001.6, X1001.8, X1001.9, X1001.10, X1001.15, X1001.18, X1001.20, X1001.25, X1001.27, X1001.30, Y1001.2 (GND); also elsewhere on the board
Lepton-1V2: C1002.1, X1001.7; also elsewhere on the board
Lepton-2V8: C1001.1, X1001.19; also elsewhere on the board
Lepton-3V0: C1003.1, C1004.1, IC1001.11 (VCCB), IC1002.2 (VCC_{1}), IC1003.11 (VCCB), R1001.1, R1003.1, R1004.2, R1005.2, X1001.16, Y1001.1 (Tri-State), Y1001.4 (VDD); also elsewhere on the board
unnamed: IC1002.7 (VCC_{2}), IC1002.8 (EN), R1006.2
unnamed: R1002.1, X1001.11
unnamed: TP1001.1, X1001.26, Y1001.3 (OUT)

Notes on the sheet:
Lepton 3.5 camera connector
DESIGN NOTE: MOSI is not used and should be grounded (see datasheet).
Level shifting (Lepton IO <> System Voltage)
[${#}] ${TITLE}

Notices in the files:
README.md:
License: GPL 3.0
